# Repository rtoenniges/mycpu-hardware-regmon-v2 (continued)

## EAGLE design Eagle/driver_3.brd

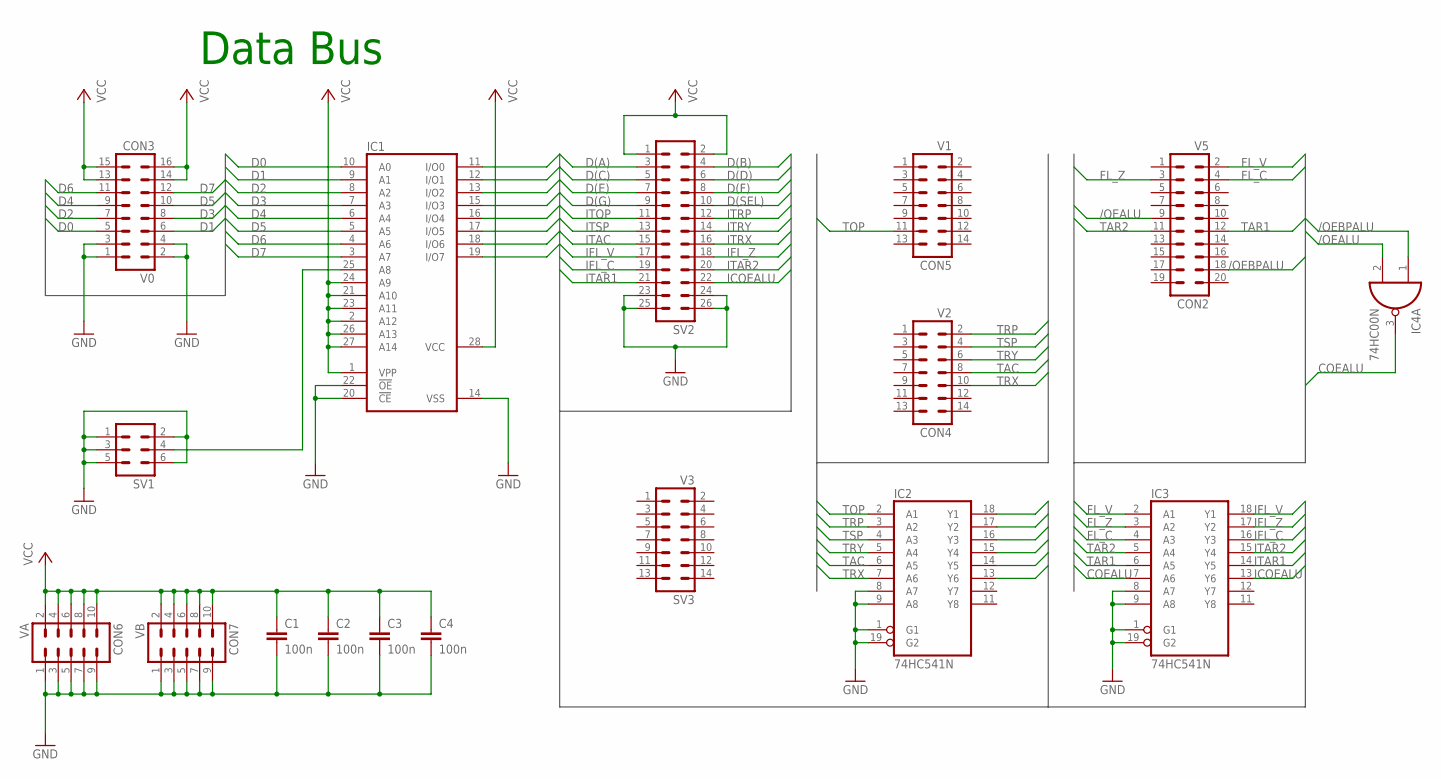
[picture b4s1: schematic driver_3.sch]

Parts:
C1, C2, C3, C4: 100n; C050-024X044
CON2: V5; ML20
CON3: V0; ML16
CON4: V2; ML14
CON5: V1; ML14
CON6: VA; ML10
CON7: VB; ML10
IC1: 27C256AG; DIL28-6
IC2, IC3: 74HC541N; DIL20
IC4: 74HC00N; DIL14
SV1: ML6
SV2: ML26L
SV3: V3; ML14

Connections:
/OEALU: CON2.9, IC4.2 (I1)
/OEBPALU: CON2.18, IC4.1 (I0)
COEALU: IC3.7 (A6), IC4.3 (O)
D0: CON3.5, IC1.10 (A0)
D1: CON3.6, IC1.9 (A1)
D2: CON3.7, IC1.8 (A2)
D3: CON3.8, IC1.7 (A3)
D4: CON3.9, IC1.6 (A4)
D5: CON3.10, IC1.5 (A5)
D6: CON3.11, IC1.4 (A6)
D7: CON3.12, IC1.3 (A7)
D(A): IC1.11 (I/O0), SV2.3
D(B): IC1.12 (I/O1), SV2.4
D(C): IC1.13 (I/O2), SV2.5
D(D): IC1.15 (I/O3), SV2.6
D(E): IC1.16 (I/O4), SV2.7
D(F): IC1.17 (I/O5), SV2.8
D(G): IC1.18 (I/O6), SV2.9
D(SEL): IC1.19 (I/O7), SV2.10
FL_C: CON2.4, IC3.4 (A3)
FL_V: CON2.2, IC3.2 (A1)
FL_Z: CON2.3, IC3.3 (A2)
GND: C1.2, C2.2, C3.2, C4.2, CON3.1, CON3.2, CON3.3, CON3.4, CON6.1, CON6.3, CON6.5, CON6.7, CON6.9, CON7.1, CON7.3, CON7.5, CON7.7, CON7.9, IC1.14 (VSS), IC1.20 (!CE), IC1.22 (!OE), IC2.1 (G1), IC2.8 (A7), IC2.9 (A8), IC2.10 (GND), IC2.19 (G2), IC3.1 (G1), IC3.8 (A7), IC3.9 (A8), IC3.10 (GND), IC3.19 (G2), IC4.7 (GND), SV1.1, SV1.2, SV1.3, SV1.5, SV1.6, SV2.23, SV2.24, SV2.25, SV2.26
ICOEALU: IC3.13 (Y6), SV2.22
IFL_C: IC3.16 (Y3), SV2.19
IFL_V: IC3.18 (Y1), SV2.17
IFL_Z: IC3.17 (Y2), SV2.18
ITAC: IC2.14 (Y5), SV2.15
ITAR1: IC3.14 (Y5), SV2.21
ITAR2: IC3.15 (Y4), SV2.20
ITOP: IC2.18 (Y1), SV2.11
ITRP: IC2.17 (Y2), SV2.12
ITRX: IC2.13 (Y6), SV2.16
ITRY: IC2.15 (Y4), SV2.14
ITSP: IC2.16 (Y3), SV2.13
unnamed: IC1.25 (A8), SV1.4
TAC: CON4.8, IC2.6 (A5)
TAR1: CON2.12, IC3.6 (A5)
TAR2: CON2.11, IC3.5 (A4)
TOP: CON5.11, IC2.2 (A1)
TRP: CON4.2, IC2.3 (A2)
TRX: CON4.10, IC2.7 (A6)
TRY: CON4.6, IC2.5 (A4)
TSP: CON4.4, IC2.4 (A3)
VCC: C1.1, C2.1, C3.1, C4.1, CON3.13, CON3.14, CON3.15, CON3.16, CON6.2, CON6.4, CON6.6, CON6.8, CON6.10, CON7.2, CON7.4, CON7.6, CON7.8, CON7.10, IC1.1 (VPP), IC1.2 (A12), IC1.21 (A10), IC1.23 (A11), IC1.24 (A9), IC1.26 (A13), IC1.27 (A14), IC1.28 (VCC), IC2.20 (VCC), IC3.20 (VCC), IC4.14 (VCC), SV2.1, SV2.2

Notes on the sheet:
Data Bus

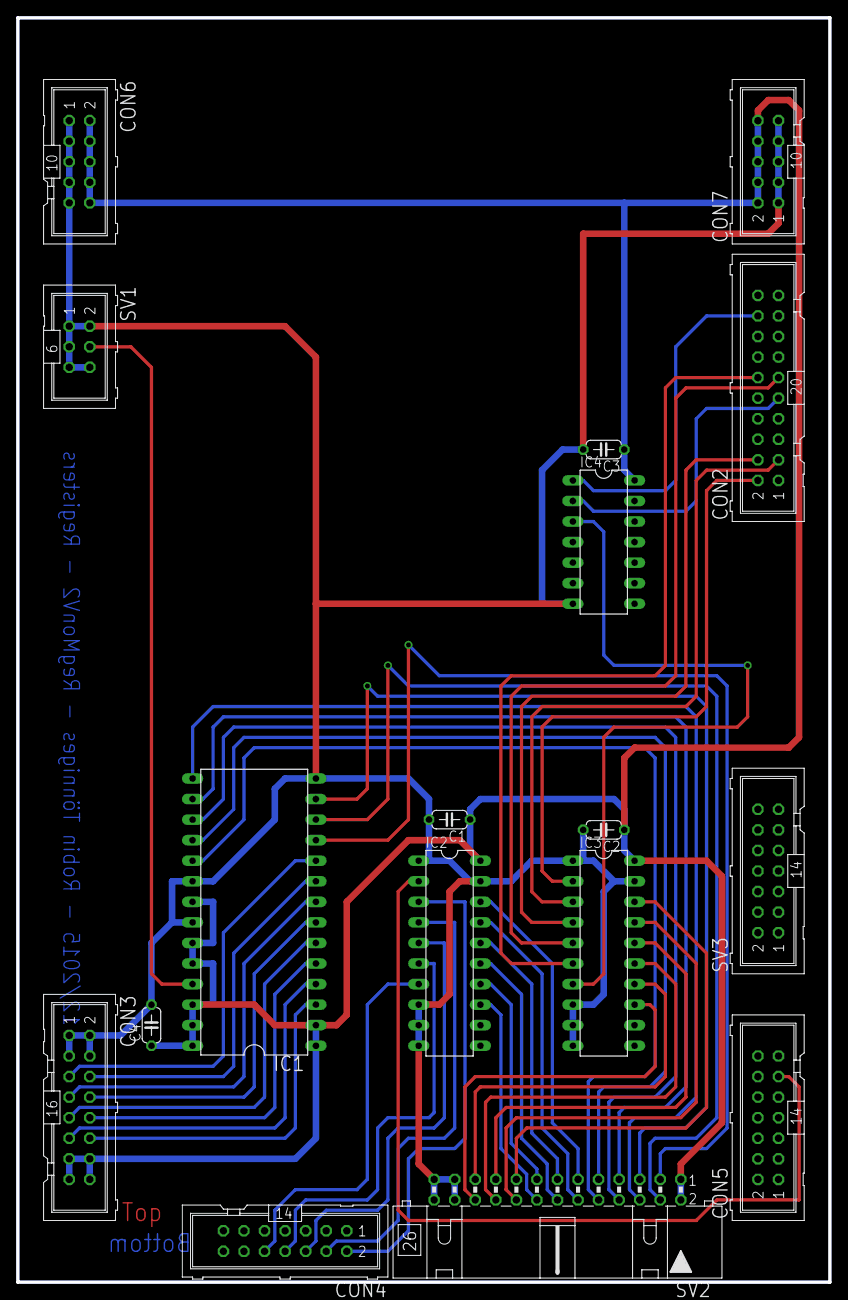
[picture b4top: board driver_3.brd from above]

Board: 2 copper layers, 100.3 x 156.2 mm, 17 parts (0 on the bottom side), 45 nets.

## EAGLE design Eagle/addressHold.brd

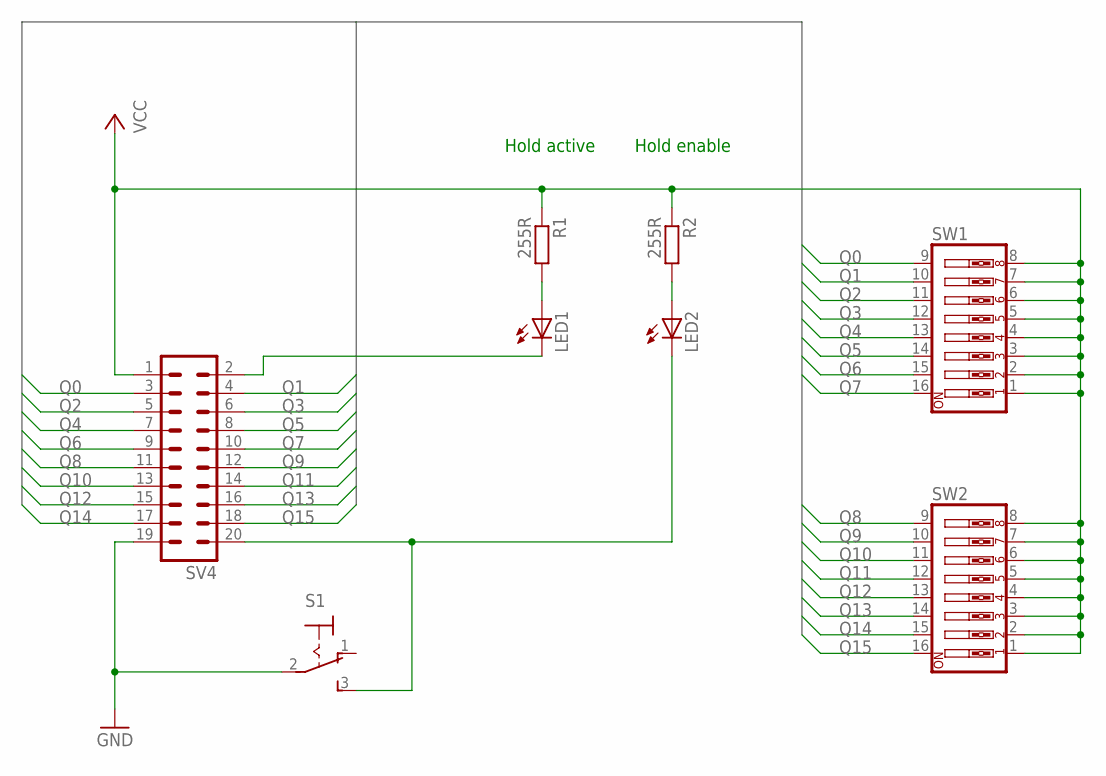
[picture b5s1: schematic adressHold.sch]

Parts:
LED1, LED2: LED5MM
R1, R2: 255R; 0204/5
S1: 320-916
SV4: ML20L
SW1, SW2: SW_DIP-8; EDG-08

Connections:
GND: S1.2, SV4.19
unnamed: LED2.K (C), S1.3 (S), SV4.20
unnamed: LED1.K (C), SV4.2
unnamed: LED1.A, R1.2
unnamed: LED2.A, R2.2
Q0: SV4.3, SW1.9
Q1: SV4.4, SW1.10
Q2: SV4.5, SW1.11
Q3: SV4.6, SW1.12
Q4: SV4.7, SW1.13
Q5: SV4.8, SW1.14
Q6: SV4.9, SW1.15
Q7: SV4.10, SW1.16
Q8: SV4.11, SW2.9
Q9: SV4.12, SW2.10
Q10: SV4.13, SW2.11
Q11: SV4.14, SW2.12
Q12: SV4.15, SW2.13
Q13: SV4.16, SW2.14
Q14: SV4.17, SW2.15
Q15: SV4.18, SW2.16
VCC: R1.1, R2.1, SV4.1, SW1.1, SW1.2, SW1.3, SW1.4, SW1.5, SW1.6, SW1.7, SW1.8, SW2.1, SW2.2, SW2.3, SW2.4, SW2.5, SW2.6, SW2.7, SW2.8

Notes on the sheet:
Hold enable
Hold active

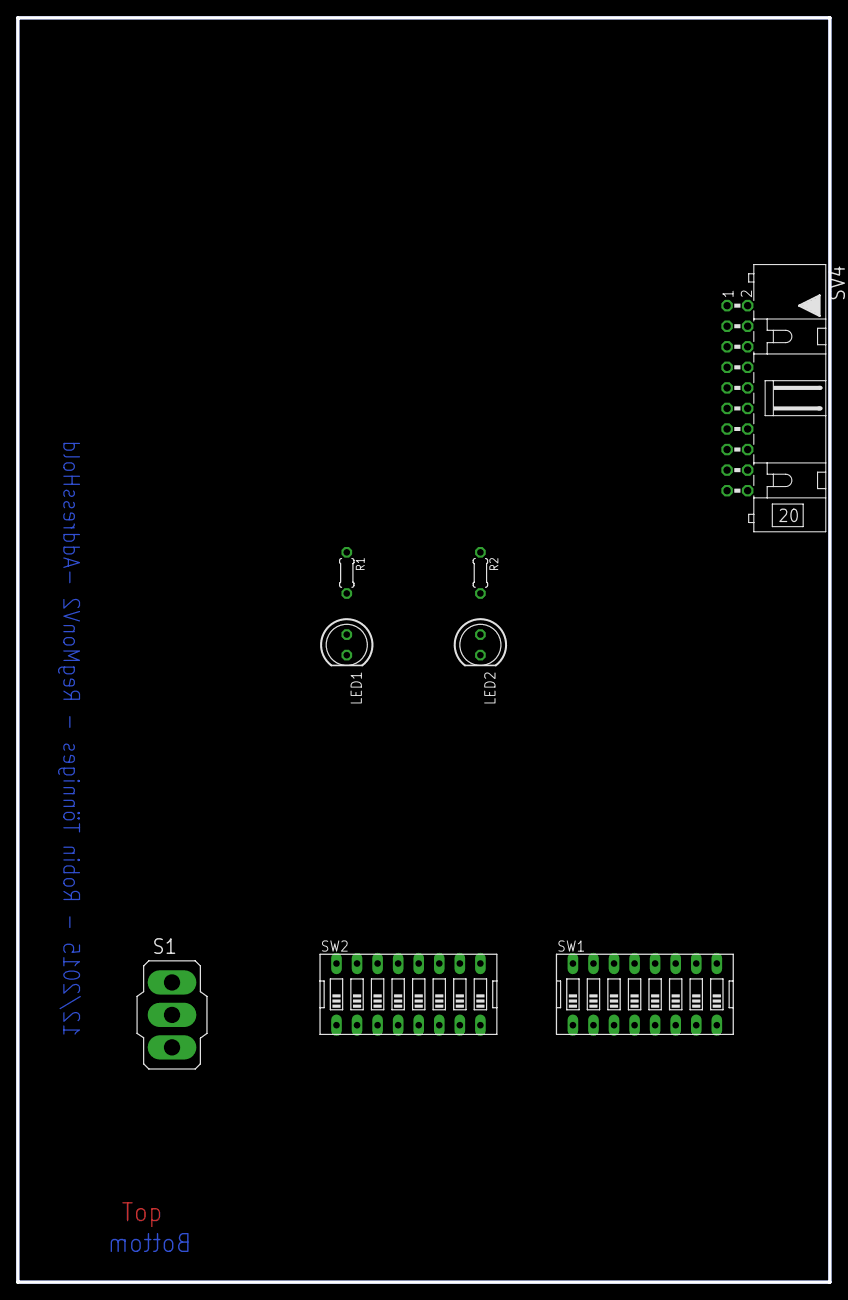
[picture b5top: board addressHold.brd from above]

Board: 2 copper layers, 100.3 x 156.2 mm, 8 parts (0 on the bottom side), 22 nets.

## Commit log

2016-03-18 Added files via upload
2016-03-18 Rename adressHold.brd to addressHold.brd
2016-03-18 Rename adressHold.sch to addressHold.sch
2017-03-01 Bug fix
    Fogrot to add a diode to /HALT Signal... very bad :-(
2017-03-20 Added licence
